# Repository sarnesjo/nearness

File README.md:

# Nearness

Minimal panning mixer for the Eurorack modular synthesizer system. Seven inputs, two outputs. The closer an input is to an output, the greater its influence on it. 3HP.

A product of the [*llllllll*](https://llllllll.co/t/prototyping-nearness-a-minimal-panning-mixer-module/8330) community.

## PCB

The [pcb](pcb) directory contains the schematic and PCB layout as a KiCad 5 project.

For convenience, the PCBs are available from OSH Park ([front](https://oshpark.com/shared_projects/fqV5h7cJ), [back](https://oshpark.com/shared_projects/oqCUYtxb)).

## Panel

The [panel](panel) directory contains a basic panel layout in SVG format, for use with a laser cutter or CNC machine.

Alternative panel designs are available:

- Joshua Goran ([files](https://llllllll.co/t/prototyping-nearness-a-minimal-panning-mixer-module/8330/66), [photos](https://llllllll.co/t/prototyping-nearness-a-minimal-panning-mixer-module/8330/92))
- Ben Moren ([repo](https://github.com/bmoren/nearness-black-gold-panel), [photos](https://llllllll.co/t/prototyping-nearness-a-minimal-panning-mixer-module/8330/112))

## Build guide

1. Start with the surface-mount components. Mind the orientation of the ICs and diodes.
2. Then do the pin headers.
3. Then the jacks.

## License

[CC BY-SA 4.0](http://creativecommons.org/licenses/by-sa/4.0/)

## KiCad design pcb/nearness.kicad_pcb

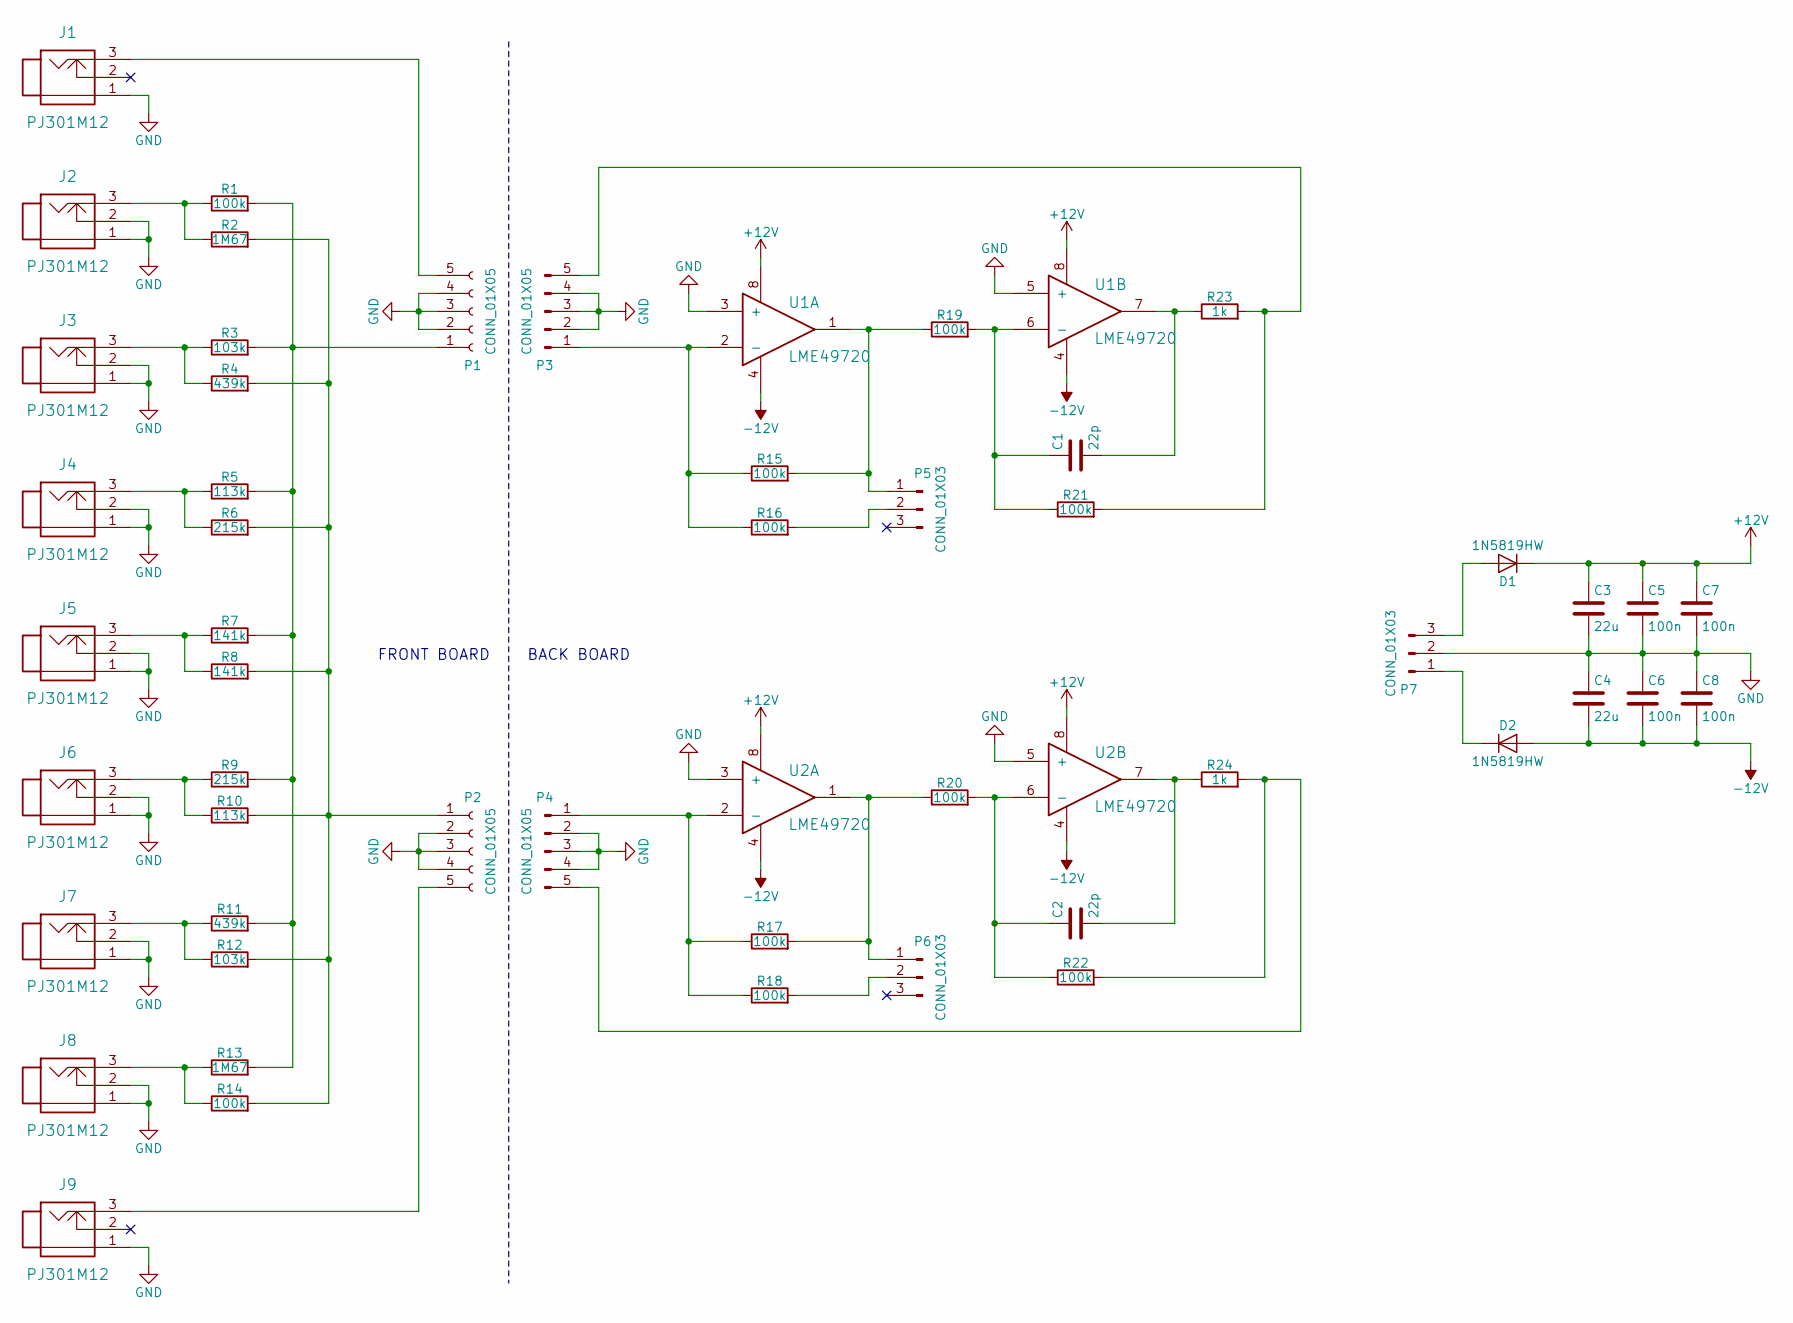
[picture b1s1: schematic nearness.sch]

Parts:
C1, C2: 22p; 0603
C3, C4: 22u; 0805
C5, C6, C7, C8: 100n; 0603
D1, D2: 1N5819HW; SOD-123
J1, J2, J3, J4, J5, J6, J7, J8, J9: PJ301M12
P1, P2, P3, P4: CONN_01X05; Pin_1x5
P5, P6: CONN_01X03; Pin_1x3
P7: CONN_01X03; Eurorack_2x5
R1, R14, R15, R16, R17, R18, R19, R20, R21, R22: 100k; 0805
R2, R13: 1M67; 0805
R3, R12: 103k; 0805
R4, R11: 439k; 0805
R5, R10: 113k; 0805
R6, R9: 215k; 0805
R7, R8: 141k; 0805
R23, R24: 1k; 0805
U1, U2: LME49720; SOIC-8

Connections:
+12V: C3.1, C5.1, C7.1, D1.1 (K), U1.8, U2.8
-12V: C4.2, C6.2, C8.2, D2.2 (A), U1.4, U2.4
GND: C3.2, C4.1, C5.2, C6.1, C7.2, C8.1, J1.1, J2.1, J2.2, J3.1, J3.2, J4.1, J4.2, J5.1, J5.2, J6.1, J6.2, J7.1, J7.2, J8.1, J8.2, J9.1, P1.2, P1.3, P1.4, P2.2, P2.3, P2.4, P3.2, P3.3, P3.4, P4.2, P4.3, P4.4, P7.2, U1.3 (+), U1.5 (+), U2.3 (+), U2.5 (+)
unnamed: C1.1, R19.2, R21.1, U1.6 (-)
unnamed: C1.2, R23.1, U1.7
unnamed: C2.1, R20.2, R22.1, U2.6 (-)
unnamed: C2.2, R24.1, U2.7
unnamed: D1.2 (A), P7.3
unnamed: D2.1 (K), P7.1
unnamed: J1.3, P1.5
unnamed: J2.3, R1.1, R2.1
unnamed: J3.3, R3.1, R4.1
unnamed: J4.3, R5.1, R6.1
unnamed: J5.3, R7.1, R8.1
unnamed: J6.3, R9.1, R10.1
unnamed: J7.3, R11.1, R12.1
unnamed: J8.3, R13.1, R14.1
unnamed: J9.3, P2.5
unnamed: P1.1, R1.2, R3.2, R5.2, R7.2, R9.2, R11.2, R13.2
unnamed: P2.1, R2.2, R4.2, R6.2, R8.2, R10.2, R12.2, R14.2
unnamed: P3.1, R15.1, R16.1, U1.2 (-)
unnamed: P3.5, R21.2, R23.2
unnamed: P4.1, R17.1, R18.1, U2.2 (-)
unnamed: P4.5, R22.2, R24.2
unnamed: P5.1, R15.2, R19.1, U1.1
unnamed: P5.2, R16.2
unnamed: P6.1, R17.2, R20.1, U2.1
unnamed: P6.2, R18.2

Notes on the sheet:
FRONT BOARD
BACK BOARD

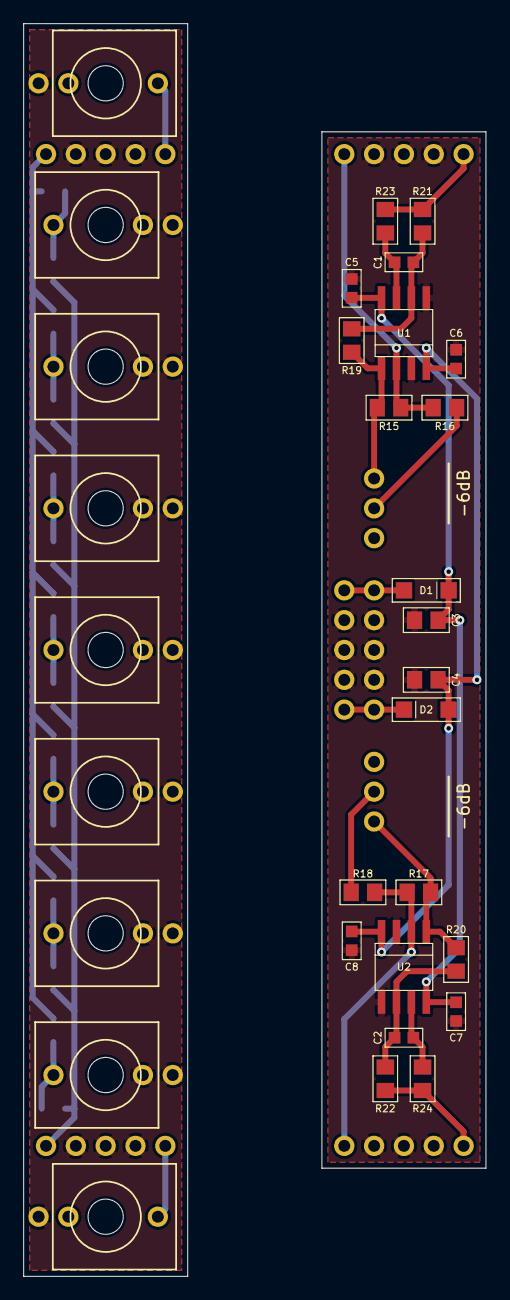
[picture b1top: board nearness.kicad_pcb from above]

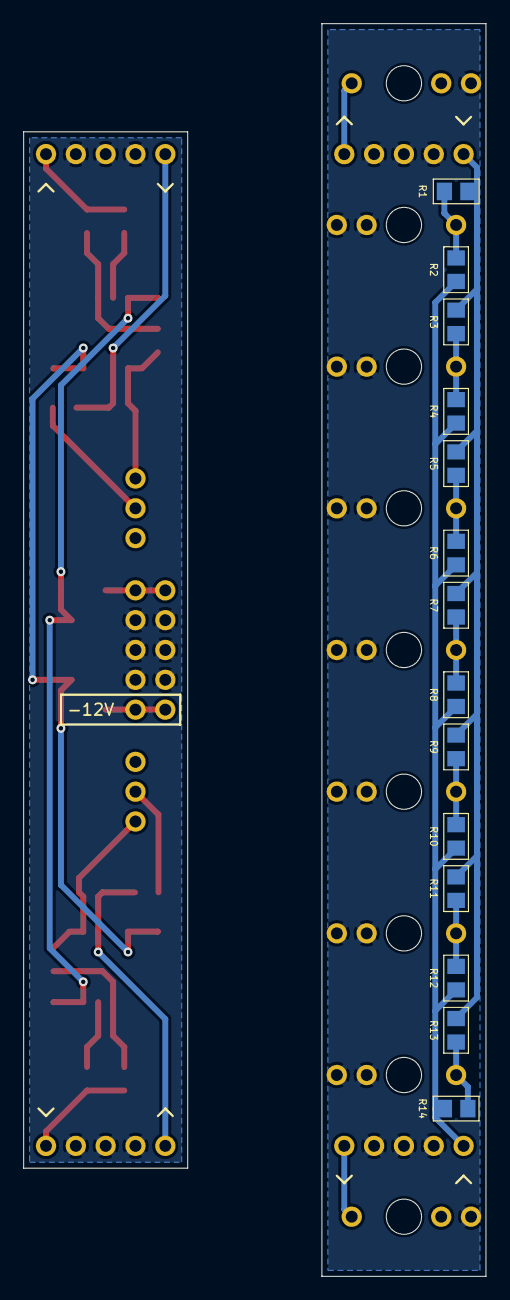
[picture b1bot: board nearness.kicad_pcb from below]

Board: 2 copper layers, 39.4 x 106.7 mm, 52 parts (15 on the bottom side), 28 nets.

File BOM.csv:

Reference,Qty,Description,Value,Package,Digikey #,Mouser #,Notes
"U1, U2",2,"IC, LME49720",,SOIC-8,LME49720MAX/NOPBCT-ND,926-LME49720MAX/NOPB,
"D1, D2",2,"Diode, 1N5819HW",,SOD-123,1N5819HW-FDICT-ND,621-1N5819HW-F,
"C1, C2",2,"Capacitor, ceramic, C0G/NP0",22p,0603,490-9685-1-ND,81-GRM185C1H220FA01J,
"C3, C4",2,"Capacitor, ceramic",22u,0805,490-10749-1-ND,81-GRM21BR61E226ME4L,
"C5, C6, C7, C8",4,"Capacitor, ceramic",100n,0603,490-9691-1-ND,81-GRM188R71E104JA1J,
"R1, R14, R15, R16, R17, R18, R19, R20, R21, R22",10,"Resistor, thin film, 0.1%",100k,0805,P100KDACT-ND,667-ERA-6AEB104V,
"R2, R13",2,"Resistor, thick film, 1%",1M69,0805,P1.69BTCT-ND,667-ERJ-6ENF1694V,
"R3, R12",2,"Resistor, thin film, 0.1%",102k,0805,P102KDACT-ND,667-ERA-6AEB1023V,
"R4, R11",2,"Resistor, thin film, 0.1%",442k,0805,P442KDACT-ND,667-ERA-6AEB4423V,
"R5, R10",2,"Resistor, thin film, 0.1%",113k,0805,P113KDACT-ND,667-ERA-6AEB1133V,
"R6, R9",2,"Resistor, thin film, 0.1%",215k,0805,P215KDACT-ND,667-ERA-6AEB2153V,
"R7, R8",2,"Resistor, thin film, 0.1%",140k,0805,P140KDACT-ND,667-ERA-6AEB1403V,
"R23, R24",2,"Resistor, thin film, 0.1%",1k,0805,P1.0KDACT-ND,667-ERA-6AEB102V,
"P1, P2",2,"Pin header, female, 1x5",,,,,http://www.taydaelectronics.com/5-pin-2-54-mm-single-row-fem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
"P3, P4",2,"Pin header, male, 1x5",,,,,http://www.taydaelectronics.com/40-pin-2-54-mm-single-row-pi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
"P5, P6",2,"Pin header, male, right angle, 1x3",,,,,http://www.taydaelectronics.com/40-pin-2-54-mm-angle-single-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
P7,1,"Pin header, male, 2x5",,,,,http://www.taydaelectronics.com/2x40-pin-2-54-mm-double-row-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
"J1, J2, J3, J4, J5, J6, J7, J8, J9",9,"Jack, PJ301M-12",,,,,https://www.thonk.co.uk/shop/3-5mm-jacks/
,2,Jumper,,,,,http://www.taydaelectronics.com/mini-jumper-2-54mm-gold-plat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

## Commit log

2018-02-20 Import files
2020-01-27 Upgrade project to KiCad 5
    Upgrade project, library, schematic, and PCB files to KiCad 5. Remap
    symbols to the Device and Connector libraries, using different symbols
    for male and female pin headers. Re-annotate schematic. Re-fill zones.
    Ignore KiCad 5 backup and cache files.
2020-01-27 Simplify panel graphics
2020-01-27 Update README
    Expand description. Add photo and links.
